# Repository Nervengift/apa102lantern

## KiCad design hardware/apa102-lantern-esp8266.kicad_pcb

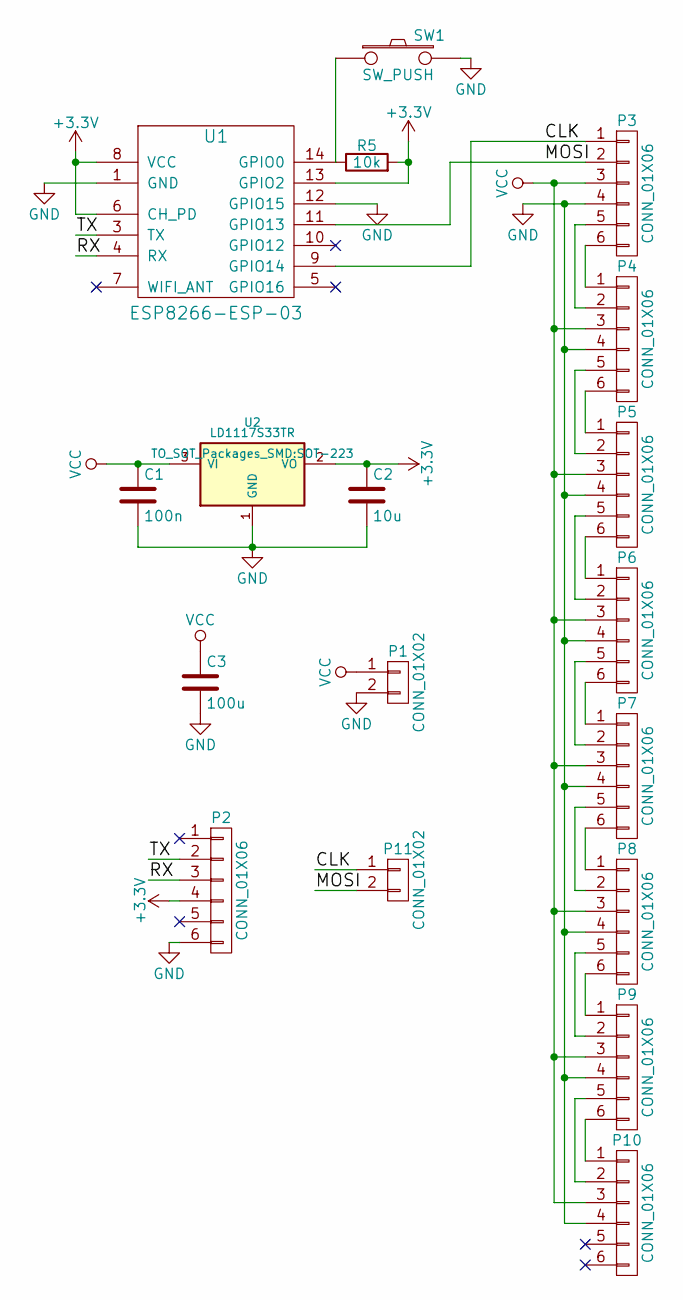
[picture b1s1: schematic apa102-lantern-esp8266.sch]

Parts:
C1: 100n; C_0603_HandSoldering
C2: 10u; C_0603_HandSoldering
C3: 100u; Elko_vert_11.5x8mm_RM3.5_CopperClear
P1, P11: CONN_01X02; Pin_Header_Straight_1x02
P2, P3, P4, P5, P6, P7, P8, P9, P10: CONN_01X06; Pin_Header_Angled_1x06
R5: 10k; R_0603_HandSoldering
SW1: SW_PUSH; SW_SPST_EVQPE1
U1: ESP8266-ESP-03
U2: LD1117S33TR; SOT-223

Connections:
+3V3: C2.1, P2.4, R5.2, U1.6 (CH_PD), U1.8 (VCC), U1.13 (GPIO2), U2.2 (VO); also elsewhere on the board
/CLK: P3.1, P11.1, U1.9 (GPIO14)
/MOSI: P3.2, P11.2, U1.11 (GPIO13)
/RX: P2.3, U1.4 (RX)
/TX: P2.2, U1.3 (TX)
GND: C1.2, C2.2, C3.2, P1.2, P2.6, P3.4, P4.4, P5.4, P6.4, P7.4, P8.4, P9.4, P10.4, SW1.2, U1.1 (GND), U1.12 (GPIO15), U2.1 (GND)
unnamed: P3.5, P4.2
unnamed: P3.6, P4.1
unnamed: P4.5, P5.2
unnamed: P4.6, P5.1
unnamed: P5.5, P6.2
unnamed: P5.6, P6.1
unnamed: P6.5, P7.2
unnamed: P6.6, P7.1
unnamed: P7.5, P8.2
unnamed: P7.6, P8.1
unnamed: P8.5, P9.2
unnamed: P8.6, P9.1
unnamed: P9.6, P10.1
unnamed: P9.5, P10.2
unnamed 24: R5.1, SW1.1, U1.14 (GPIO0); also elsewhere on the board
VCC: C1.1, C3.1, P1.1, P3.3, P4.3, P5.3, P6.3, P7.3, P8.3, P9.3, P10.3, U2.3 (VI)

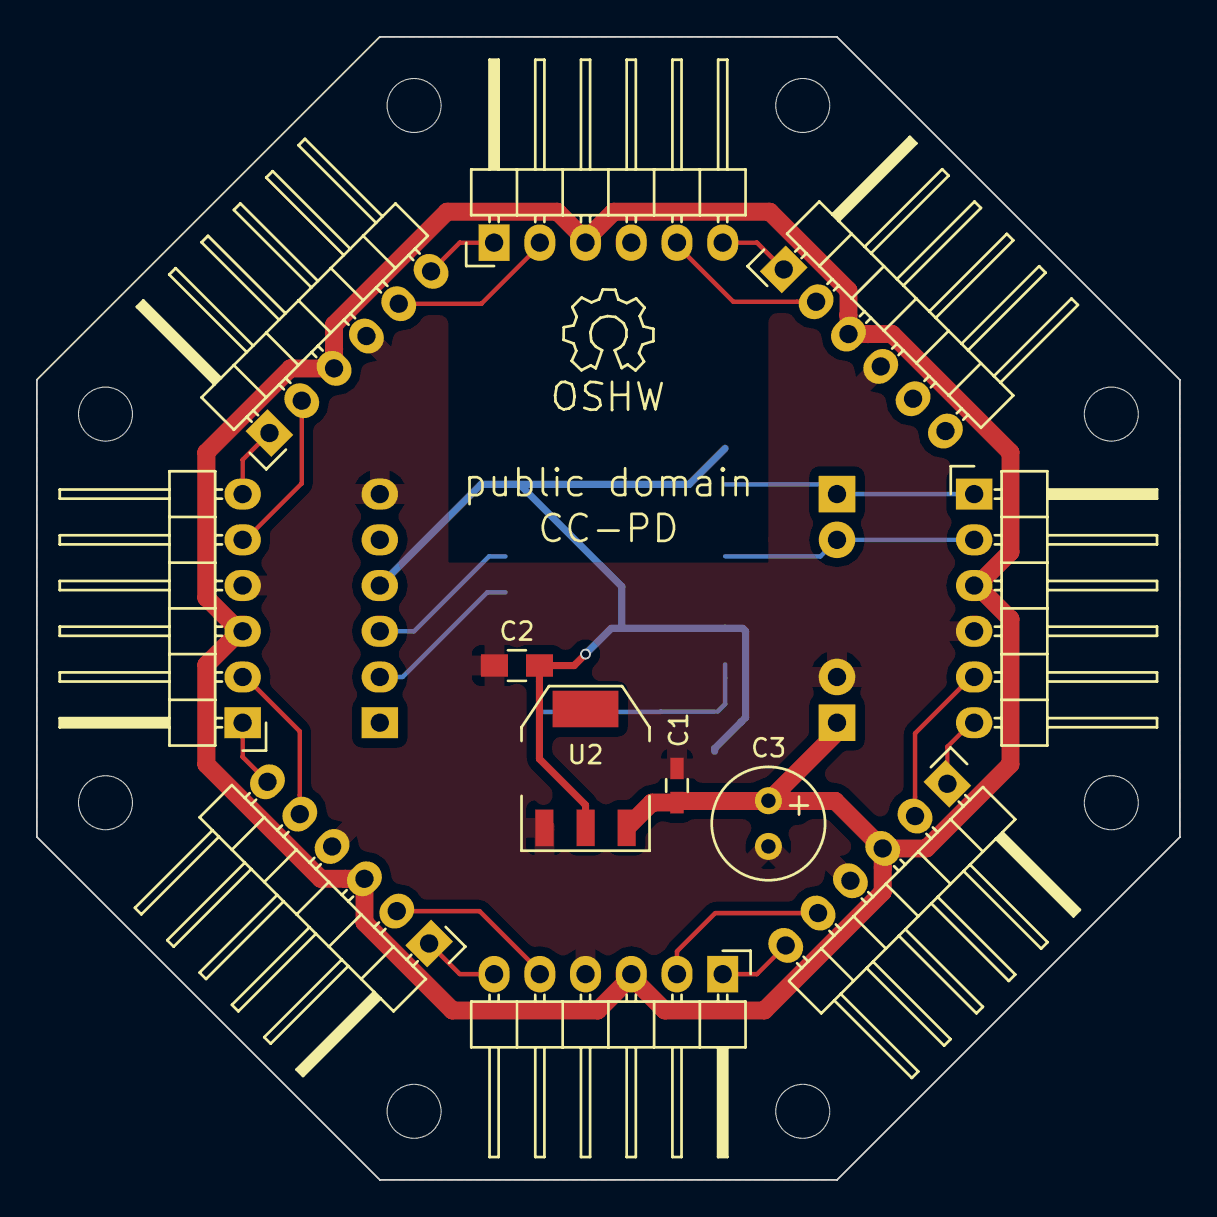
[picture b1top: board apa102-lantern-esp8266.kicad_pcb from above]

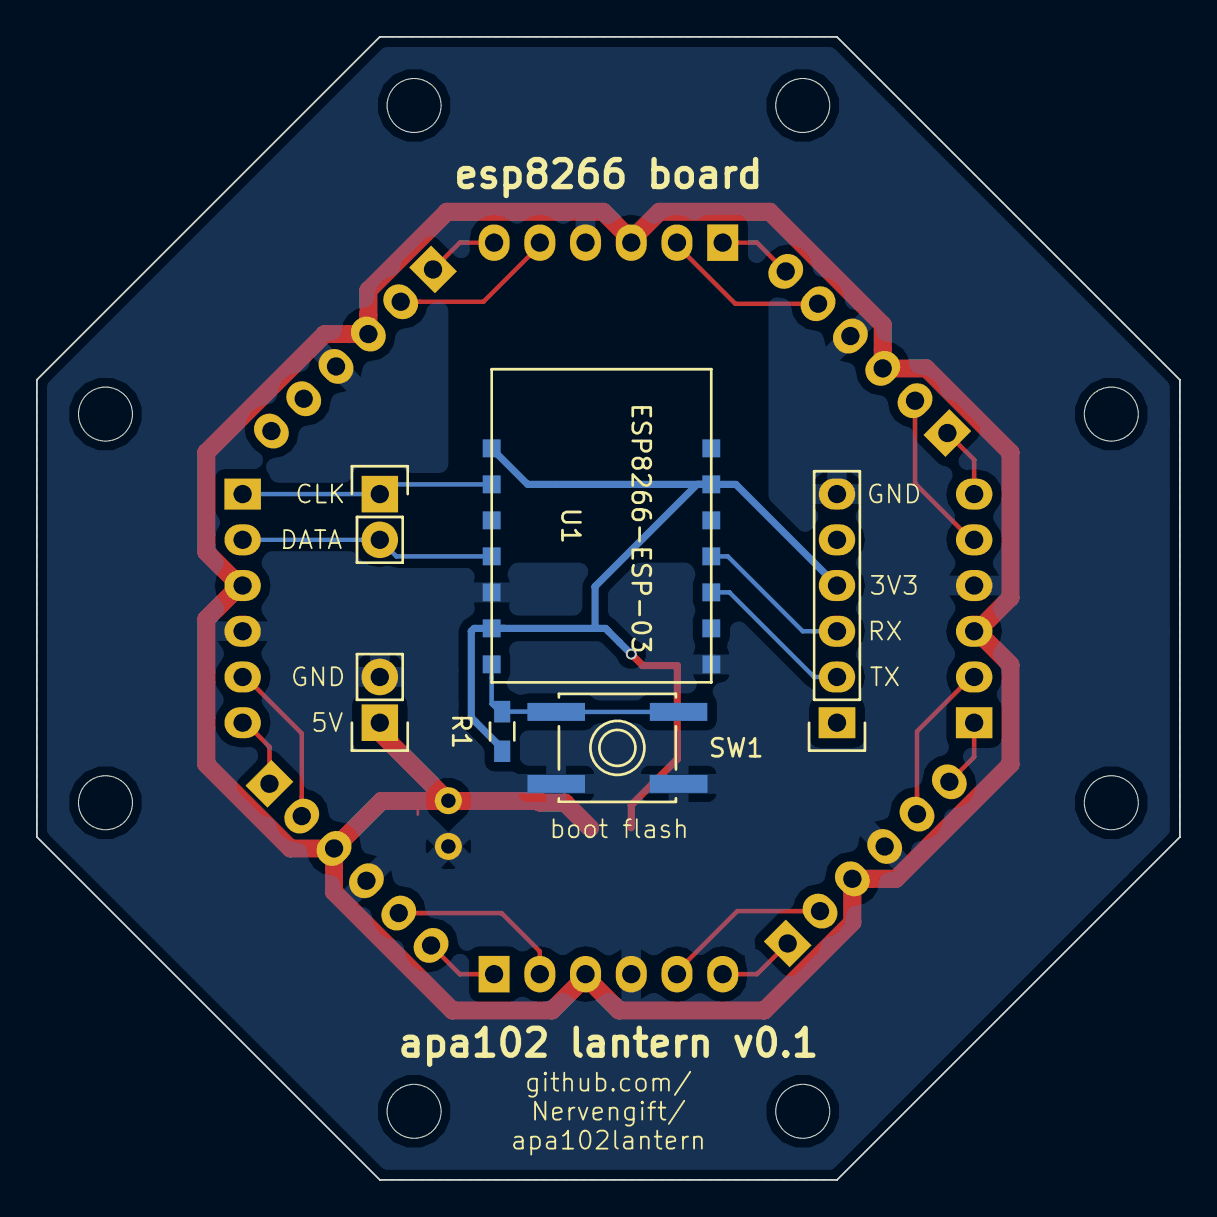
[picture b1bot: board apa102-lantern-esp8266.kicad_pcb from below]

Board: 2 copper layers, 63.5 x 63.5 mm, 18 parts (6 on the bottom side), 22 nets.

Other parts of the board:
R1: 10k; R_0603_HandSoldering

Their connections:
+3V3: R1.2; also elsewhere on the board
unnamed 24: R1.1; also elsewhere on the board

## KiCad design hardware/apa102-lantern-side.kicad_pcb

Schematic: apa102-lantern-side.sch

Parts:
P1, P2: CONN_01X06; Pin_Header_Straight_1x06
U1, U2, U3, U4, U5, U6, U7, U8: APA102

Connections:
/5V: P1.3, P2.3, U1.4, U2.4, U3.4, U4.4, U5.4, U6.4, U7.4, U8.4; also elsewhere on the board
/>D: P1.2, U1.1
/>clk: P1.1, U1.2
/D>: P1.5, U8.6
/GND: P1.4, P2.1, P2.2, P2.4, P2.5, P2.6, U1.3, U2.3, U3.3, U4.3, U5.3, U6.3, U7.3, U8.3; also elsewhere on the board
/clk>: P1.6, U8.5
unnamed: U1.5, U2.2
unnamed: U1.6, U2.1
unnamed: U2.5, U3.2
unnamed: U2.6, U3.1
unnamed: U3.5, U4.2
unnamed: U3.6, U4.1
unnamed: U4.5, U5.2
unnamed: U4.6, U5.1
unnamed: U5.5, U6.2
unnamed: U5.6, U6.1
unnamed: U6.5, U7.2
unnamed: U6.6, U7.1
unnamed: U7.5, U8.2
unnamed: U7.6, U8.1

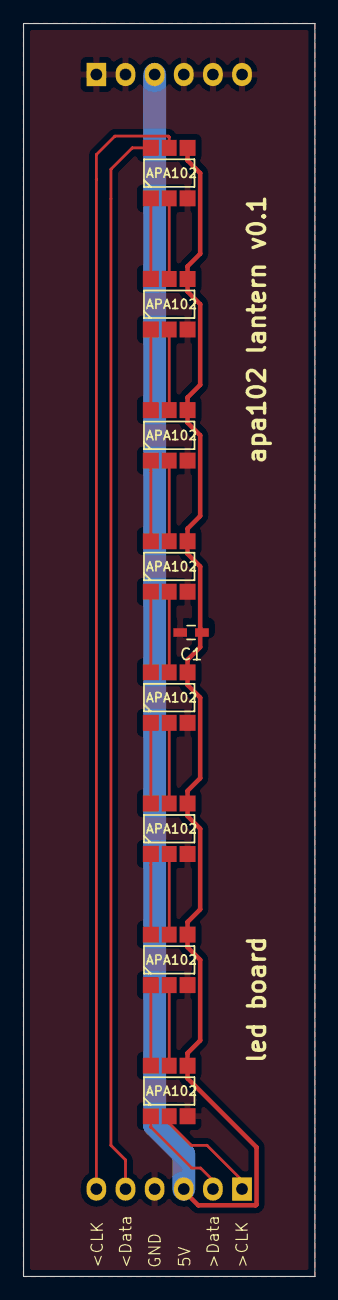
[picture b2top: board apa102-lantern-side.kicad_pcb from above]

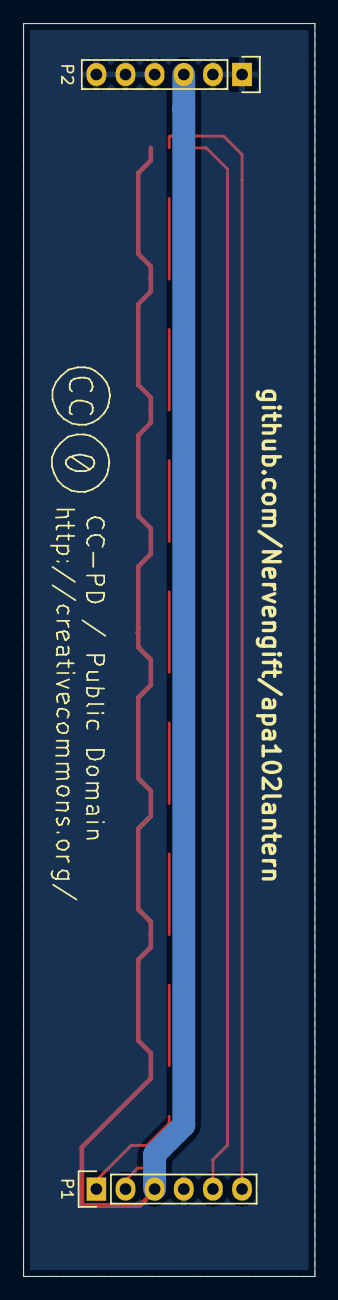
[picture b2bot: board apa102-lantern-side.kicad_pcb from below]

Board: 2 copper layers, 25.4 x 109.2 mm, 11 parts (2 on the bottom side), 20 nets.

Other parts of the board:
C1: 0.1u; C_0603_HandSoldering

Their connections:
/5V: C1.1; also elsewhere on the board
/GND: C1.2; also elsewhere on the board

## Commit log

2015-10-04 Adds github url to pcbs
2015-10-04 Adds pins to access the leds directly via SPI
2015-10-06 Fix pin headers and add VCC on 2nd pin panel
2015-10-06 Adds license to esp board silkscreen
2015-10-06 Adds a capacitor on the led board (just to be sure)
2015-10-06 Fixes traces that where lost somehow
2015-10-06 Silkscreen fixes
2015-10-06 Bigger footprint for C3
2015-10-15 Preparations for fabrication

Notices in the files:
hardware/apa102-lantern-esp8266.kicad_pcb:
public domain
